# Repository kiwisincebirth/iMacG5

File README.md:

iMacG5
======

This is an Arduino (Leonardo) project that implements a System Management Controller on a Apple iMac that has been converted to a Hackintosh replacing the original G5 motherboard with an Intel Haswell NUC D54250. See the following for full details of the project:

http://www.tonymacx86.com/completed-mods/139633-kiwis-20-imac-i5.html

The software (and hardware) provide System management function including
 * Management of full power management lifecycle.
 * Control of shutdown of original G5 ATX PSU
 * Control of LCD backlight inverter brightness from Mac Menu widget
 * Control of screen Brightnes via Mac Menu application (via USB serial)
 * Fan Speed Control from internal temperature monitoring
 * Front Panel LED and Power Switch control

This repository contains
 * The full Bill of Materials for the Hardware
 * The source code for Arduino microcontroller
 * The source code for the Brightness Menu on the Mac

This application also has code to support capacative touch sensors as used by MacTester in his excellent iMac creations. Thanks for hs contribution to this project.

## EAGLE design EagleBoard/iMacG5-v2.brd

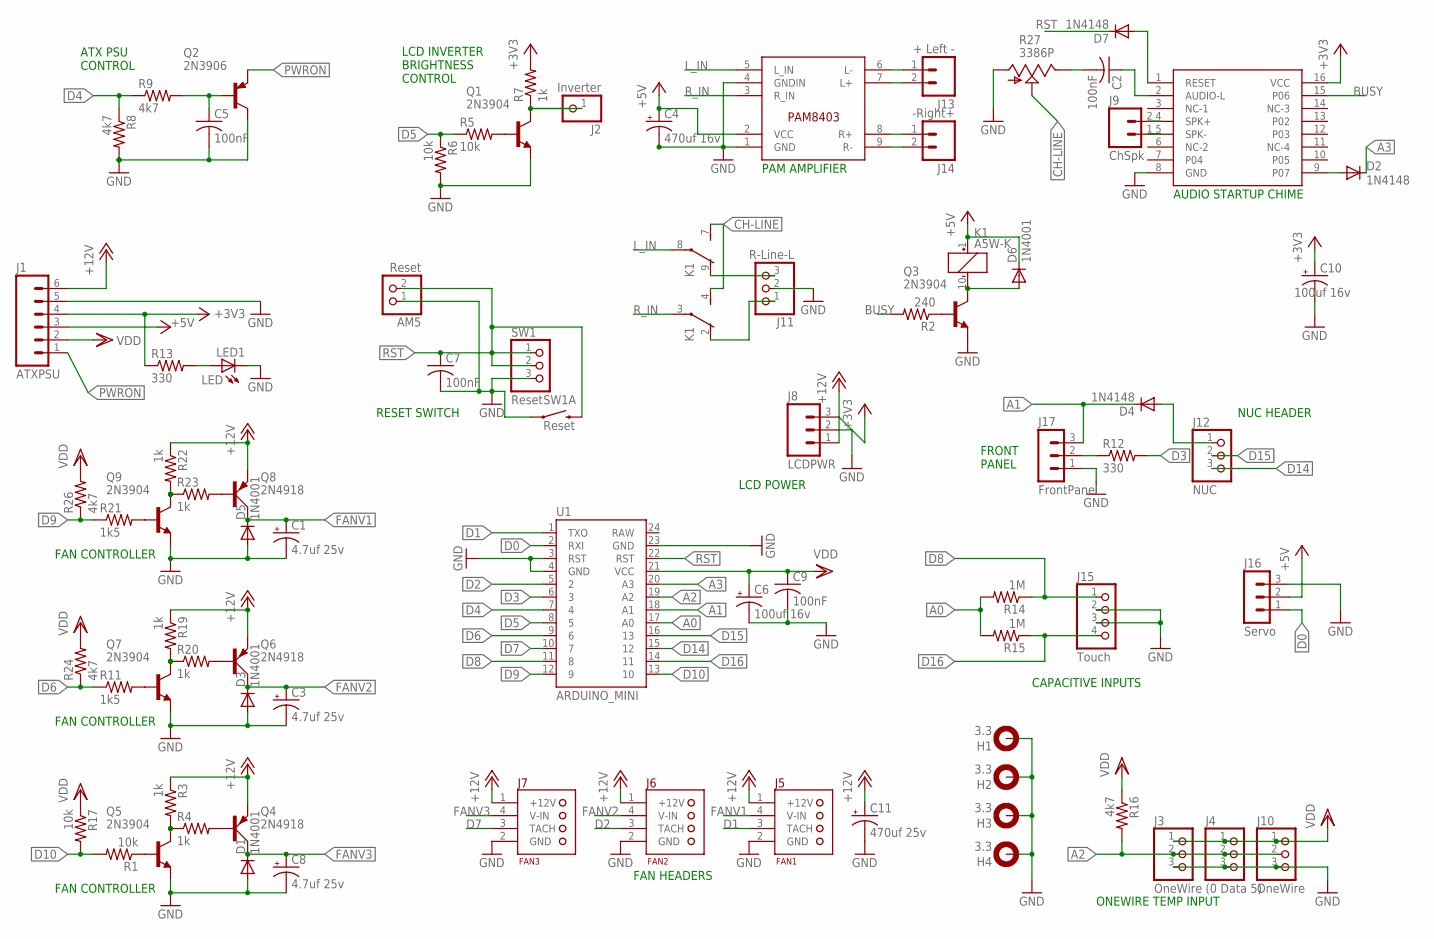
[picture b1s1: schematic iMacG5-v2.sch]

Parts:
AM5: Reset; 1X02
C1, C3, C8: 4.7uf 25v; E2,5-5
C2, C5, C7, C9: 100nF; C050-024X044
C4: 470uf 16v; E3,5-8
C6, C10: 100uf 16v; E2,5-5
C11: 470uf 25v; E3,5-8
D1, D3, D5: 1N4001; D-2.5
D2, D4: 1N4148; D-2.5
D6: 1N4001; D-7.5
D7: 1N4148; DO35-7
H1, H2, H3, H4: 3.3; 3,3-PAD
J1: ATXPSU; MOLEX-1X6
J2: Inverter; 1X01
J3, J10: OneWire; 1X03
J4: (0 Data 5); 1X03
J5: FAN1; MOLEX-1X4
J6: FAN2; IMAC_G5_2X3
J7: FAN3; IMAC_G5_2X3
J8: LCDPWR; MOLEX-1X3
J9: ChSpk; MOLEX-1X2
J11: R-Line-L; 1X03
J12: NUC; 1X03
J13: + Left -; MOLEX-1X2
J14: -Right+; MOLEX-1X2
J15: Touch; 1X04
J16: Servo; MA03-1
J17: FrontPanel; MA03-1
K1: A5W-K; TQ2
LED1: LED; LED3MM
Q1, Q3, Q5, Q7, Q9: 2N3904; TO92
Q2: 2N3906; TO92
Q4, Q6, Q8: 2N4918; TO126AV
R1, R17: 10k; 0207/7
R2: 240; 0207/2V
R3, R4, R7, R19, R20, R22, R23: 1k; 0207/2V
R5, R6: 10k; 0207/2V
R8, R9, R24, R26: 4k7; 0207/2V
R11, R21: 1k5; 0207/2V
R12, R13: 330; 0207/2V
R14, R15: 1M; 0207/7
R16: 4k7; 0207/7
R27: 3386P; B25P
SW1: Reset; 1X03
SW1A: Reset; TACTILE-PTH
U1: ARDUINO_MINI
U2: PAM8403
U3: WTV020-SD-16P

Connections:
+3V3: C10.+, J1.4, J8.3, R7.2, R13.1, U3.16 (VCC)
+5V: C4.+, D6.C, J1.3, J16.2, K1.1 (+), U2.2 (VCC)
+12V: C11.+, J1.6, J5.1 (+12V), J6.1 (+12V), J7.1 (+12V), J8.1, Q4.E, Q6.E, Q8.E, R3.1, R19.1, R22.1
A0: R14.2, R15.2, U1.17 (A0)
A1: D4.C, J17.3, U1.18 (A1)
A2: J3.2, J4.2, J10.2, R16.2, U1.19 (A2)
A3: D2.C, U1.20 (A3)
BUSY: R2.2, U3.15 (P06)
CH-LINE: K1.4 (S), K1.7 (S), R27.S
D0: J16.1, U1.2 (RXI)
D1: J5.3 (TACH), U1.1 (TXO)
D2: J6.3 (TACH), U1.5 (2)
D3: R12.2, U1.6 (3)
D4: R8.1, R9.1, U1.7 (4)
D5: R5.1, R6.1, U1.8 (5)
D6: R11.1, R24.1, U1.9 (6)
D7: J7.3 (TACH), U1.10 (7)
D8: J15.1, R14.1, U1.11 (8)
D9: R21.1, R26.1, U1.12 (9)
D10: R1.2, R17.2, U1.13 (10)
D14: J12.3, U1.15 (12)
D15: J12.2, U1.16 (13)
D16: J15.4, R15.1, U1.14 (11)
FANV1: C1.+, D5.C, J5.4 (V-IN), Q8.C
FANV2: C3.+, D3.C, J6.4 (V-IN), Q6.C
FANV3: C8.+, D1.C, J7.4 (V-IN), Q4.C
GND: AM5.1, C1.-, C3.-, C4.-, C5.2, C6.-, C7.2, C8.-, C9.2, C10.-, C11.-, D1.A, D3.A, D5.A, H1.B3,3, H2.B3,3, H3.B3,3, H4.B3,3, J1.5, J3.3, J4.3, J5.2 (GND), J6.2 (GND), J7.2 (GND), J8.2, J10.3, J11.2, J15.2, J15.3, J16.3, J17.1, LED1.K (C), Q1.3 (E), Q2.1 (C), Q3.3 (E), Q5.3 (E), Q7.3 (E), Q9.3 (E), R6.2, R8.2, R27.A, SW1.3, SW1A.1, U1.3 (RST), U1.4 (GND), U1.23 (GND), U2.1 (GND), U2.4 (GNDIN), U3.8 (GND)
L_IN: K1.8, U2.5 (L_IN)
unnamed: D4.A, J12.1
unnamed: D6.A, K1.10 (-), Q3.1 (C)
unnamed: Q1.2 (B), R5.2
unnamed: Q4.B, R4.2
unnamed: Q5.1 (C), R3.2, R4.1
unnamed: J2.1, Q1.1 (C), R7.1
unnamed: J9.1, U3.5 (SPK-)
unnamed: J9.2, U3.4 (SPK+)
unnamed: J17.2, R12.1
unnamed: J14.1, U2.8 (R+)
unnamed: D7.A, U3.1 (RESET)
unnamed: C2.2, R27.E
unnamed: J14.2, U2.9 (R-)
unnamed: Q5.2 (B), R1.1
unnamed: J13.2, U2.7 (L+)
unnamed: Q6.B, R20.2
unnamed: LED1.A, R13.2
unnamed: J11.3, K1.9 (O)
unnamed: J11.1, K1.2 (O)
unnamed: Q3.2 (B), R2.1
unnamed: D2.A, U3.9 (P07)
unnamed: J13.1, U2.6 (L-)
unnamed: Q7.1 (C), R19.2, R20.1
unnamed: Q7.2 (B), R11.2
unnamed: Q8.B, R23.2
unnamed: Q9.1 (C), R22.2, R23.1
unnamed: Q9.2 (B), R21.2
unnamed: C5.1, Q2.2 (B), R9.2
unnamed: C2.1, U3.2 (AUDIO-L)
PWRON: J1.1, Q2.3 (E)
RST: AM5.2, C7.1, D7.C, SW1.1, SW1.2, SW1A.3 (2), U1.22 (RST)
R_IN: K1.3, U2.3 (R_IN)
VDD: C6.+, C9.1, J1.2, J3.1, J4.1, J10.1, R16.1, R17.1, R24.2, R26.2, U1.21 (VCC)

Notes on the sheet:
FAN HEADERS
PAM AMPLIFIER
CAPACITIVE INPUTS
AUDIO STARTUP CHIME
FAN CONTROLLER
NUC HEADER
FRONT PANEL
ONEWIRE TEMP INPUT
LCD INVERTER BRIGHTNESS CONTROL
ATX PSU CONTROL
RESET SWITCH
LCD POWER

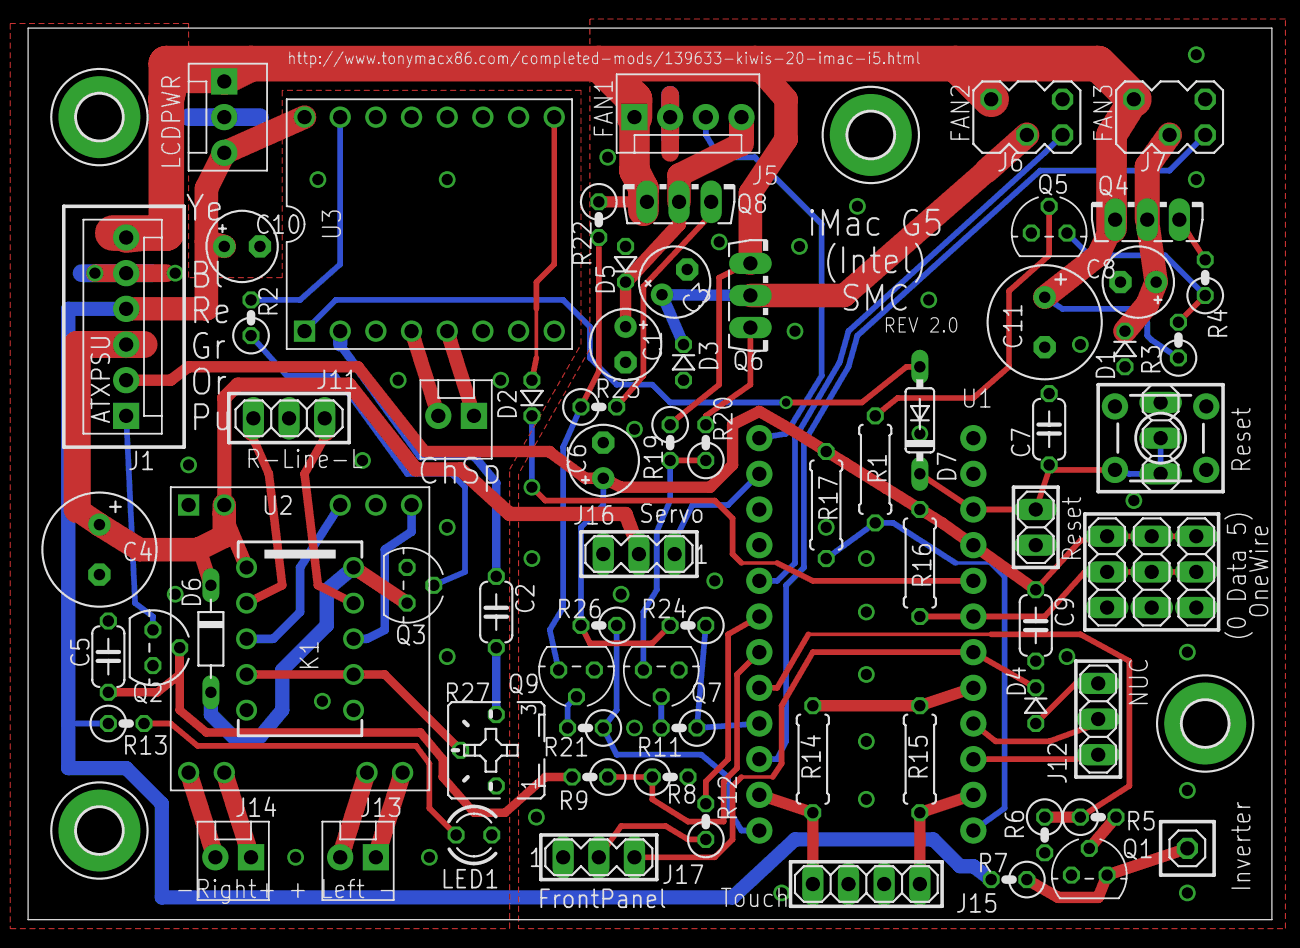
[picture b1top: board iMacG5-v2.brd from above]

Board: 2 copper layers, 88.6 x 63.5 mm, 80 parts (0 on the bottom side), 61 nets.

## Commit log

2014-07-26 Initial
    Initial Upload of Source Code
2014-08-09 Minor Updates
2014-08-09 Added Significant Debug Code for testing FSM
2014-08-09 Fixes for startup issues, Power Button Activiation
    Significant fixes in startup code with Power button simulation and
    detection code. Added significant debugging messages.
2014-08-09 Misc Changes
2014-08-09 Fix Merge Problem
2014-08-20 Changed the Project URL to the completed Build
2014-09-21 Added Bill of Materials
    Added Bill of Materials
2014-12-28 Added Brightness Menulet
    This is the complete source code for Brightness Menulet, (runs on Mac)
    that allows the brightness to be controlled (via USB) to the Arduino
    micro controller
2014-12-28 Added comments about the Brightness Menu Control
2014-12-28 Formatting
2015-01-23 First Test of Fan RPM Code
2015-01-23 Fixes and Testing of Fan RPM Code
2015-01-25 Small tidyup, defined and used pin constants.
2015-01-31 Support Update of Existing SMC
2015-01-31 Final Fixes after Debug
2015-01-31 Small Code Cleanup
2015-01-31 Cleanup of Fan Code, Removed Redundant
2015-01-31 Improved RPM Control
2015-01-31 Fixed Issue with EEPROM writes
2015-01-31 More Fixes to Capacitive
2015-01-31 BUG FIX For fan RPMS
2015-02-06 Removed LED Flash Command Code
2015-02-06 Fixed ReadOnly in EPROM
2015-02-06 Added time statistics
2015-02-06 Added more reporting metricscalc
2015-02-06 Add counting Total Elapsed System LCD time
2015-02-06 Added Total Wake Time
2015-02-07 Improved System Reporting
2015-02-15 Initial Support for Rev2 SMC
2015-02-15 Further REV 2 Support. Still Issues
2015-02-15 Fixed #iffef compiler Problem
2015-02-15 More work to get RPM controlled Fans
2015-02-16 A lot of work to align Code to New Control
2015-02-17 Further Fan work and Code Cleanup.
2015-02-18 Small addition of stepped PWM change
2015-02-18 Stepping added to Legacy.
2015-02-18 More Code cleanup
2015-02-18 Revert "Improved System Reporting"
    This reverts commit 43092c34f74c30da4868c2d6cb2a2ff94bc2fcef.
2015-02-18 Revert 43092c3..606fe0a
    This rolls back to commit 43092c34f74c30da4868c2d6cb2a2ff94bc2fcef.
2015-02-18 Fixes to capactive Code
2015-02-18 Minimal Changes
2015-02-18 More simple Fixes, compatibility
2015-02-19 Small Fix
2015-02-19 Revert 997a22c..606fe0a
    This rolls back to commit 997a22c1ea8c0d0d6c7038b4ded34150e8846562.
2015-02-19 Working Control using RPM
2015-02-21 Small Changes
2015-02-21 Changed the upper Maximum
2015-02-21 Added ST (Temp) Command
2015-02-24 Added Eagle Files
2015-04-11 Changed ifDef to Modern
2015-04-19 Mac Testers Menulet from Post 99, and Firmware Change
2015-04-19 Tidy think to do with source tree
2015-04-19 GITIGNORE
2015-04-20 Fixed the horizontal alignment issue
2015-05-31 Changes by Mac tester in Final released Build
2015-05-31 Fix Issue with Horizontal alignment
2015-05-31 Feature improvement of the Arduino Code to support new Menu Command
2015-05-31 Fixed to correctly display degC in terminal
2015-05-31 Added Feature to turn LED on when inverter is Off.
2015-08-08 Small Minor changes for Modern Board
2015-08-09 Small Improvements and attempt to fix Fans
2015-08-09 BIG CHANGE
2015-08-11 Simplify the code, but not tested
2015-08-14 Bug Fix
2015-08-14 Fix Compile Errors
2015-08-14 Remove Legacy Code
2015-08-14 Removed commented Fan Code
2015-08-15 Reinstated Fan RPM
2015-08-15 Fan Logic just Fan 2 being controlled
2015-08-15 Simple fixes
2015-08-29 small fixes

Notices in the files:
parts and their libraries:
SparkFun-Boards: Licensing: Creative Commons ShareAlike 4.0 International - https://creativecommons.org/licenses/by-sa/4.0
